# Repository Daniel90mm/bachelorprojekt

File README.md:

# Bachelorprojekt: Prototype Pulsoximeter

Repository til bachelorprojektets notebooks, måledata, referencedokumenter
og KiCad-hardwaredesign for en prototypisk pulsoximeter til ikke-invasiv
måling af arteriel iltmætning (SpO₂).

Systemet bruger to multipleksede LED'er ved 660 nm og 940 nm, en
Hamamatsu S1223 fotodiode og en analog signalkæde med transimpedans-
forstærker, andenordens Sallen-Key lavpasfilter og et ikke-inverterende
gain-trin. Det optiske interface er en modulær 3D-printet fingerklemme,
og signalindsamling og -behandling håndteres af en Analog Discovery 3
og en Python-pipeline baseret på ratio-of-ratios-metoden.

Den fulde rapport ligger som [thesis.pdf](thesis.pdf).

## Resultater (live demo)

- HR: (51.7 ± 0.3) BPM
- SpO₂: (95.8 ± 1.5) %: proof of concept, ikke klinisk kalibreret
- LED-bølgelængder: 664.99 nm (FWHM 18.30 nm) og 951.79 nm (FWHM 27.25 nm)

## Struktur

- [notebooks/](notebooks/): Jupyter-notebooks til analyse, plots, målinger og kalibrering.
- [data/](data/): måledata, kalibreringstabeller, livemålinger og genererede plots.
- [docs/](docs/): diagrammer og instrumentkalibrering brugt til dokumentation.
- [hardware/kicad/](hardware/kicad/): KiCad-printprojekt og produktionsfiler.
- [references/](references/): datablade og artikler brugt som projektreferencer.
- [thesis.pdf](thesis.pdf): den endelige rapport.

## Vigtige filer

- [notebooks/filtre.ipynb](notebooks/filtre.ipynb): Bode-analyse af LPF- og HPF-trin.
- [notebooks/plots.ipynb](notebooks/plots.ipynb): spektrale plots, LED-sammenligninger og projektfigurer.
- [notebooks/optokæde.ipynb](notebooks/optokæde.ipynb): simulering af hele optokæden fra LED til signal.
- [notebooks/hyperspektral_pixelanalyse.ipynb](notebooks/hyperspektral_pixelanalyse.ipynb): pixelanalyse af hyperspektrale .tif-billeder.
- [notebooks/spektrometer.ipynb](notebooks/spektrometer.ipynb): spektrometeranalyse.
- [notebooks/lineær_stage_kalibrering.ipynb](notebooks/lineær_stage_kalibrering.ipynb): kalibrering af lineær stage.
- [live_pulsoximeter_måling.py](live_pulsoximeter_måling.py): selvstændig liveprototype til måling af HR og SpO₂.
- [plot_pulsoximeter_målinger.py](plot_pulsoximeter_målinger.py): genererer rapportplots fra livemålingerne.
- [data/live/](data/live/): livemålinger brugt til rapportens demonstrationsplots.
- [data/calibration/](data/calibration/): kalibreringsdata og rå Bode-målinger.
- [data/plots/](data/plots/): eksportklare figurer til rapport og præsentation.
- [hardware/kicad/](hardware/kicad/): kredsløbsdiagram, PCB-layout og produktionsfiler.
- [references/datasheets/](references/datasheets/): datablade for centrale komponenter.

## Krav og installation

- Python 3.10 eller nyere.
- Digilent WaveForms SDK installeret (kræves af `dwfpy` for at tale med Discovery 3).

```bash
python -m venv .venv
source .venv/bin/activate    # Windows: .venv\Scripts\activate
pip install -r requirements.txt
```

## Live pulsoximeter

Kør livevisning med popout-plot:

```bash
python live_pulsoximeter_måling.py --cycle-rate 7.41
```

Regenerer rapportplots fra livemålingerne i [data/live/](data/live/):

```bash
python plot_pulsoximeter_målinger.py
```

## Noter

- Lokale editorfiler, Jupyter-cache, KiCad-låse-/historikfiler og genererede backup-zipfiler ignoreres.
- Løse WaveForms-eksporter og rå livemålinger i repo-roden ignoreres.
  Rå kalibreringsmålinger ligger i [data/calibration/](data/calibration/),
  navngivne livemålinger i [data/live/](data/live/), og færdige figurer
  ligger i [data/plots/](data/plots/).

## Licens

MIT: se [LICENSE](LICENSE).

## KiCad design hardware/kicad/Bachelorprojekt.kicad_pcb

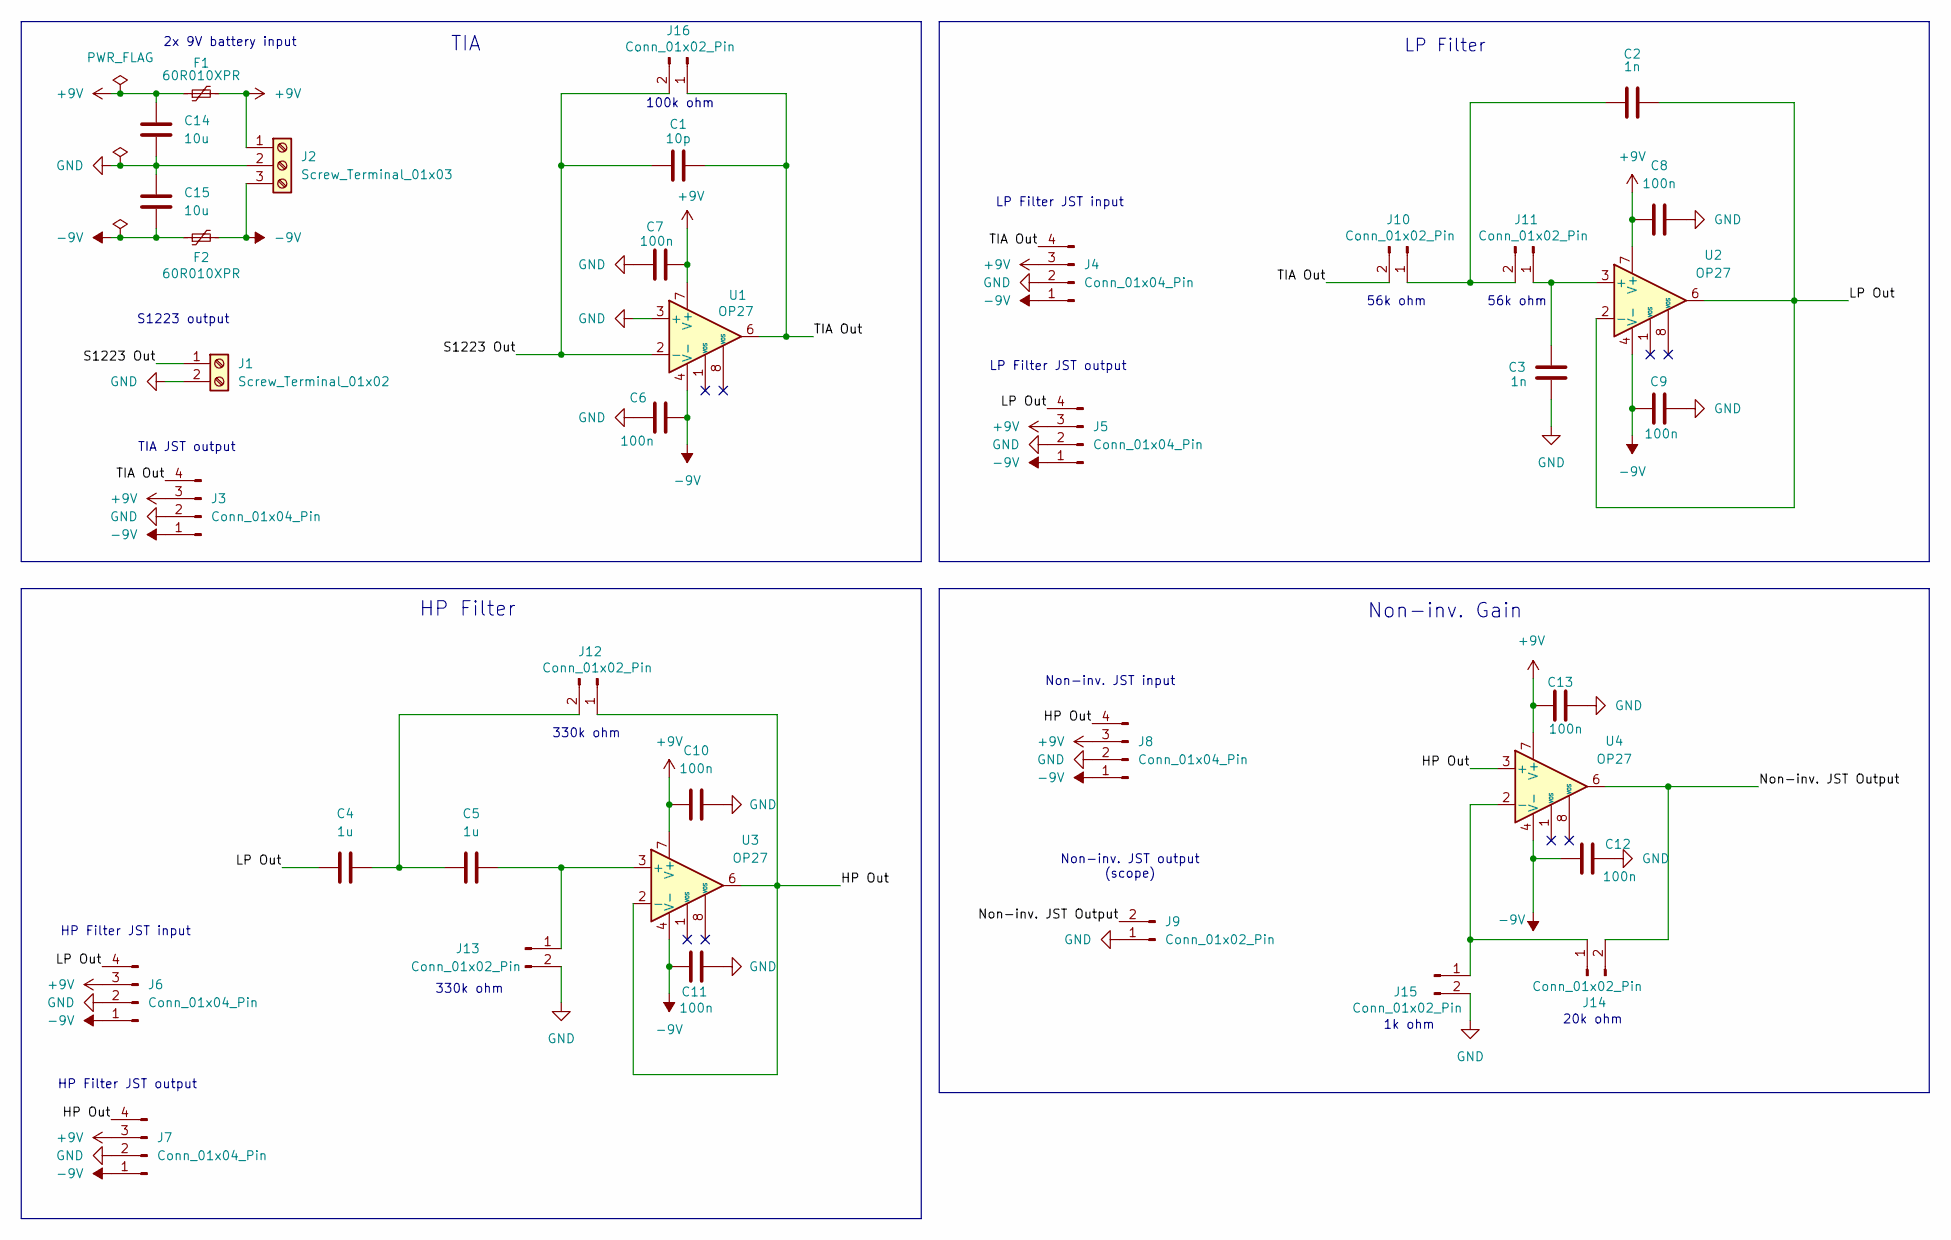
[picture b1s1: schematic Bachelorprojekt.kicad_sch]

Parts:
C1: 10p; C_Disc_D5.0mm_W2.5mm_P2.50mm
C2, C3: 1n; C_Rect_L7.0mm_W3.5mm_P5.00mm
C4, C5: 1u; C_Rect_L7.2mm_W7.2mm_P5.00mm_FKS2_FKP2_MKS2_MKP2
C6, C7, C8, C9, C10, C11, C12, C13: 100n; C_Rect_L7.0mm_W3.5mm_P5.00mm
C14, C15: 10u; C_Rect_L7.0mm_W4.5mm_P5.00mm
F1, F2: 60R010XPR; Fuse_Bourns_MF-RG300
J1: Screw_Terminal_01x02; TerminalBlock_MaiXu_MX126-5.0-02P_1x02_P5.00mm
J2: Screw_Terminal_01x03; TerminalBlock_MaiXu_MX126-5.0-03P_1x03_P5.00mm
J3, J4, J5, J6, J7, J8: Conn_01x04_Pin; JST_XH_B4B-XH-A_1x04_P2.50mm_Vertical
J9: Conn_01x02_Pin; JST_XH_B2B-XH-A_1x02_P2.50mm_Vertical
J10, J11, J12, J13, J14, J15, J16: Conn_01x02_Pin; PinSocket_1x02_P2.54mm_Vertical
U1, U2, U3, U4: OP27; DIP-8_W7.62mm_Socket

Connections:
+9V: C7.2, C8.1, C10.1, C13.1, C14.1, F1.1, F1.2, J2.1, J3.3, J4.3, J5.3, J6.3, J7.3, J8.3, U1.7 (V+), U2.7 (V+), U3.7 (V+), U4.7 (V+)
-9V: C6.2, C9.1, C11.1, C12.1, C15.2, F2.1, F2.2, J2.3, J3.1, J4.1, J5.1, J6.1, J7.1, J8.1, U1.4 (V-), U2.4 (V-), U3.4 (V-), U4.4 (V-)
/HP Out: J7.4, J8.4, J12.1, U3.2 (-), U3.6, U4.3 (+)
/LP Out: C2.2, C4.1, J5.4, J6.4, U2.2 (-), U2.6
/Non-inv. JST Output: J9.2, J14.2, U4.6
/S1223 Out: C1.1, J1.1, J16.2, U1.2 (-)
/TIA Out: C1.2, J3.4, J4.4, J10.2, J16.1, U1.6
GND: C3.1, C6.1, C7.1, C8.2, C9.2, C10.2, C11.2, C12.2, C13.2, C14.2, C15.1, J1.2, J2.2, J3.2, J4.2, J5.2, J6.2, J7.2, J8.2, J9.1, J13.2, J15.2, U1.3 (+)
unnamed: C2.1, J10.1, J11.2
unnamed: C3.2, J11.1, U2.3 (+)
unnamed: C4.2, C5.1, J12.2
unnamed: C5.2, J13.1, U3.3 (+)
unnamed: J14.1, J15.1, U4.2 (-)

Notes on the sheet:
1k ohm
20k ohm
TIA
HP Filter
S1223 output
Non-inv. JST output (scope)
LP Filter JST output
HP Filter JST output
Non-inv. Gain
56k ohm
HP Filter JST input
TIA JST output
Non-inv. JST input
2x 9V battery input
LP Filter
330k ohm
100k ohm
LP Filter JST input

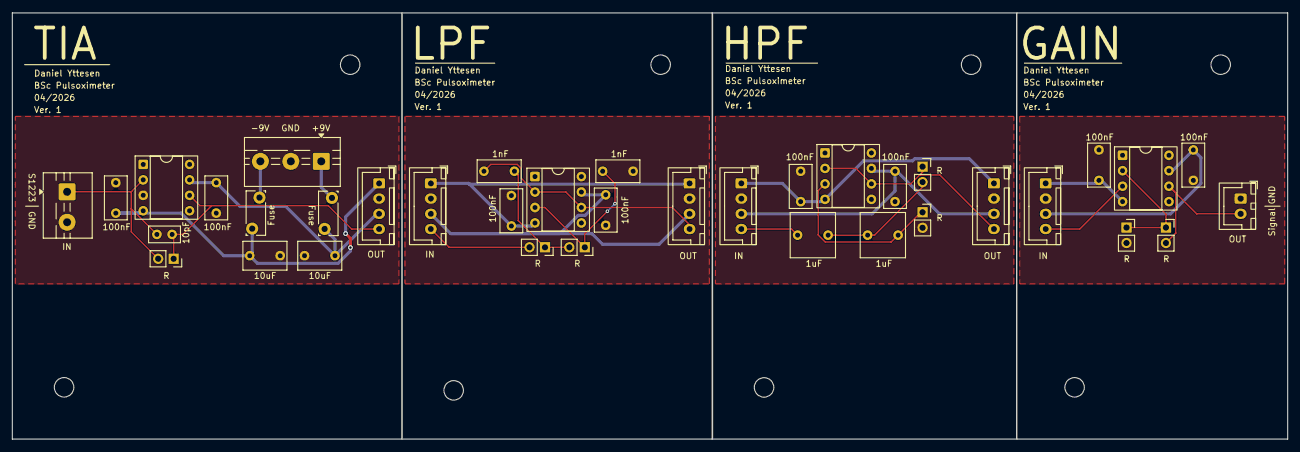
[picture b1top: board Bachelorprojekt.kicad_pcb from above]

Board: 2 copper layers, 209.5 x 70.0 mm, 37 parts (0 on the bottom side), 13 nets.

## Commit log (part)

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2026-02-04 Tilføjer lokale filer til repository
2026-02-04 Tilføjer KiCad kredsløb
2026-02-24 Tilføjer spektrometer.ipynb
2026-03-23 marts 23
2026-05-03 Strukturer projektfiler og ryd op
2026-05-06 Tilføj dansk liveprototype til pulsoximeter
2026-05-06 Organiser projektdata og danske repo-regler
2026-05-06 Tilføj licens og danske filnavne
2026-05-07 Ensret notebook- og datamappenavne til dansk snake_case
    - Omdøb notebooks til lowercase snake_case med æøå:
    filtre, plots, spektrometer, optokæde, arbejdslog,
    hyperspektral_pixelanalyse, lineær_stage_kalibrering.
    - Omdøb data/raw/daniel/leder/ til lysdioder/ for tydelighed.
    - Slet ubrugt 3Dprint.ipynb.
    - Flyt rå Bode-screenshots fra repo-roden til data/calibration/
2026-05-10 Opdater kalibrering og pulsoximeterdata
2026-05-23 Tilføj endelige kalibreringsmålinger og hardwarefiler
2026-05-23 Forenkl live pulsoximeterberegninger
2026-05-24 Opdater målecyklus for live pulsoximeter
2026-05-25 Vent på nok målinger
2026-05-26 Aflever bachelorprojekt: ryd op og tilføj rapport
    - Tilføj thesis.pdf (færdig rapport)
    - Flyt navngivne livemålinger til data/live/ og opdater plot-script
    - Flyt finger_930nm_roi_regioner.png til data/plots/
    - Fjern overskydende _metrics.csv, repeat_*-kalibreringsruns og Præsentation.odp
    - Udvid README med projektoversigt, resultater og links til centrale filer
    - Udvid .gitignore med løse rådata og logs i repo-rod
2026-05-26 Gør arbejdslog lokal og tilpas README
    - Ignorer notebooks/arbejdslog.ipynb og fjern den fra repoet
    - Fjern navnehenvisning ved lineær_stage_kalibrering
    - Erstat em-dashes med kolon/bindestreg i README
2026-05-26 Fjern henvisning til privat thesis-only repo i README
